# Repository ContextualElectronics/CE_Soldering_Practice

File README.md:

CE_Soldering_Practice
=====================

A board for learning how to solder without breaking anything.  This one is supposed to act as a little example circuit to show the amplication effect of a 741 opamp on an oscillating signal.  The 555 outputs a squarewave at around 100hz, which then passes through an RC filter to soften the edges of the square and then another capacitor to remove the DC component of the signal.

Because the signal that is fed into the 741 isn't a true square anymore, you can actually see when the amp gets saturated, and see the variations in amplification due to changing the resistor values more easily on an oscilloscope.

As of 27-JAN-2014, the headers are designed as follows...

Middle board 3 socket header: +9v, -9v and Ground (two 9v batteries in series, with the center as ground reference).

End Board 7 pin header: 1. Oscilloscope test point: pre-amp
                        2. Oscilloscope test point: post-amp
                        3. Oscilloscope Ground
                        4. Signal Resistor IN 
                        5. Signal Resistor OUT 
                        6. Feedback Resistor IN 
                        7. Feedback Resistor OUT

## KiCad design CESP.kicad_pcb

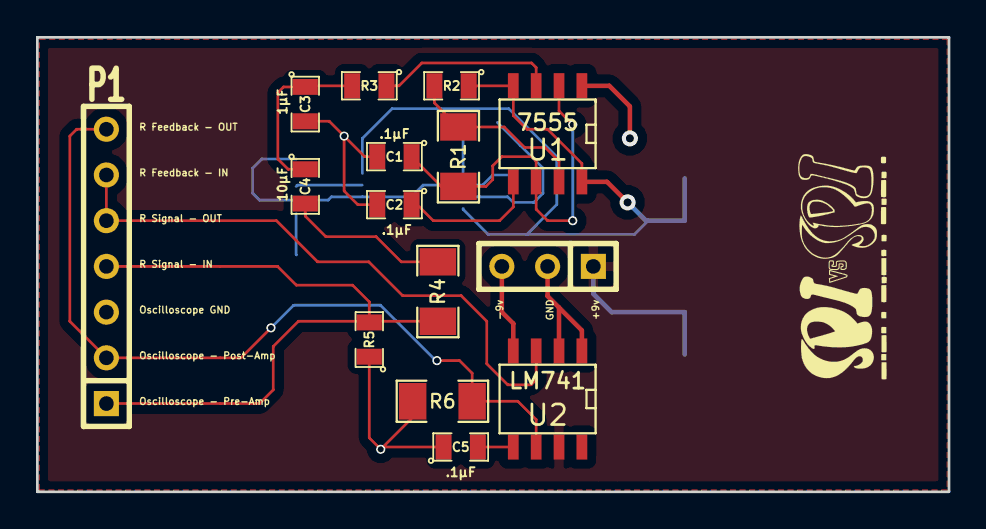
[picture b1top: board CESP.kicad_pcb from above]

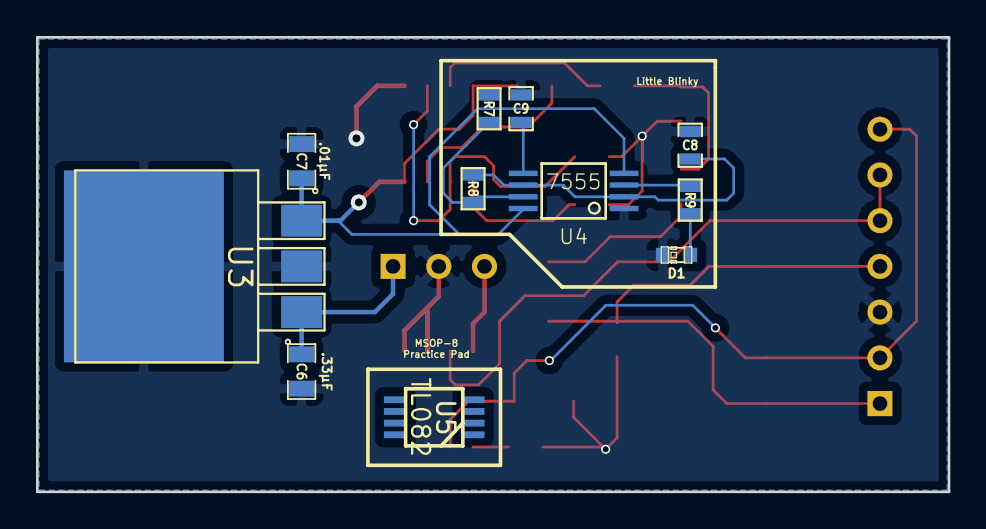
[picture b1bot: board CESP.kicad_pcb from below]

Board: 2 copper layers, 50.6 x 25.2 mm, 27 parts (11 on the bottom side), 19 nets.

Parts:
C1, C2, C5: .1µF; SM0805
C3: 1µF; SM0805
C4: 10µF; SM0805
C6: .33µF; SM0805
C7: .01µF; SM0805
C8: 10µF; SM0603_Capa
C9: .1µF; SM0603_Capa
D1: LED; LED-0603
K1: CONN_3; SIL-3
P1: CONN_7; SIL-7
R1: 68K; SM1206
R2, R3, R5: 1K; SM0805
R4: 10K; SM1206
R6: 2K2; SM1206
R7: 4K7; SM0603
R8: 180K; SM0603
R9: 330; SM0603
U1: 7555; SO8E
U2: LM741; SO8E
U3: 7805-REG; DPAK3
U4: 7555; TSSOP-8
U5: TL082; MSOP_8
VAL: SPIvsSPI_1; SPIvsSPI_500

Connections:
-9V: K1.3, U2.4
GND: C1.2, C2.2, C3.2, C5.1, C6.2, C7.2, C8.1, C9.1, D1.2, K1.2, P1.3, R5.1, R6.1, U1.1, U2.1, U2.2, U3.2, U4.1
unnamed: P1.1, P1.4, R4.1, R5.2
unnamed: P1.5, P1.6, U2.3
unnamed: R9.1, U4.3
unnamed: D1.1, R9.2
unnamed: C9.2, U4.5
unnamed: R7.1, R8.2, U4.7
unnamed: C8.2, R8.1, U4.2, U4.6
unnamed: C1.1, R1.2, U1.2, U1.6
unnamed: C2.1, U1.5
unnamed: R1.1, R2.2, U1.7
unnamed: R3.1, U1.3
unnamed: C4.2, R4.2
unnamed: C5.2, U2.5
unnamed: P1.2, P1.7, R6.2, U2.6
unnamed: C3.1, C4.1, R3.2
unnamed: C7.1, R2.1, R7.2, U1.4, U1.8, U3.3, U4.4, U4.8
VCC: C6.1, K1.1, U2.7, U3.1

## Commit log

2014-01-24 Initial Commit
    A dummy project for CE members to download (to test GitHub) and start
    creating their own CE Soldering Practice board.
2014-01-27 First draft of schematic
    First draft of having added and connected items in the schematic,
    annotated and sized the devices and added a netlist.
2014-01-27 Post ERC...
2014-01-27 First draft of PCB layout
    It's a total mess, but I got it to pass ERC, have the 7805 connected,
    used a bunch of different foot prints, used vias and successfully beat
    my head against the brickwall of KiCad.
2014-01-27 Several PCB layout drafts later...
2014-01-28 And yet further PCB layout drafts...
    ... I'm beginning to truly despise this board. I think it has it out
    for me.
2014-01-28 Added headers and SPI vs SPI logo...
    Headers added to allow customizing the Signal and Feedback resistors.
    Headers added to allow measurement with an oscilloscope.
    SPI vs. SPI logo from John Lohe added.
2014-01-28 Revised logo...
2014-01-28 Removed old components...
    There was a resistor left over that has been replaced by headers. The
    board passes DRC now.
2014-01-28 Completed Gerbers - Oshpark can process
2014-01-28 Added large footprint
2014-01-28 Revert "Added large footprint"
    This reverts commit b333fd873bfd8b188279f3009577f26e7c66da37.
2014-01-28 Added TSSOP, MSOP and regenerated gerbers...
    1. TSSOP 555 blinky circuit added with teeny components to backside
    copper.
    2. MSOP pads added to back, not connected to anything.
    3. Gerbers updated. Trial run through OshPark for validation
    successful.
2017-05-06 Added a new file extension to ignore
